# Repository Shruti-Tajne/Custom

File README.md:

# PCB
A simple LED ciruit with USB-C as power. Custom PCB for gifting

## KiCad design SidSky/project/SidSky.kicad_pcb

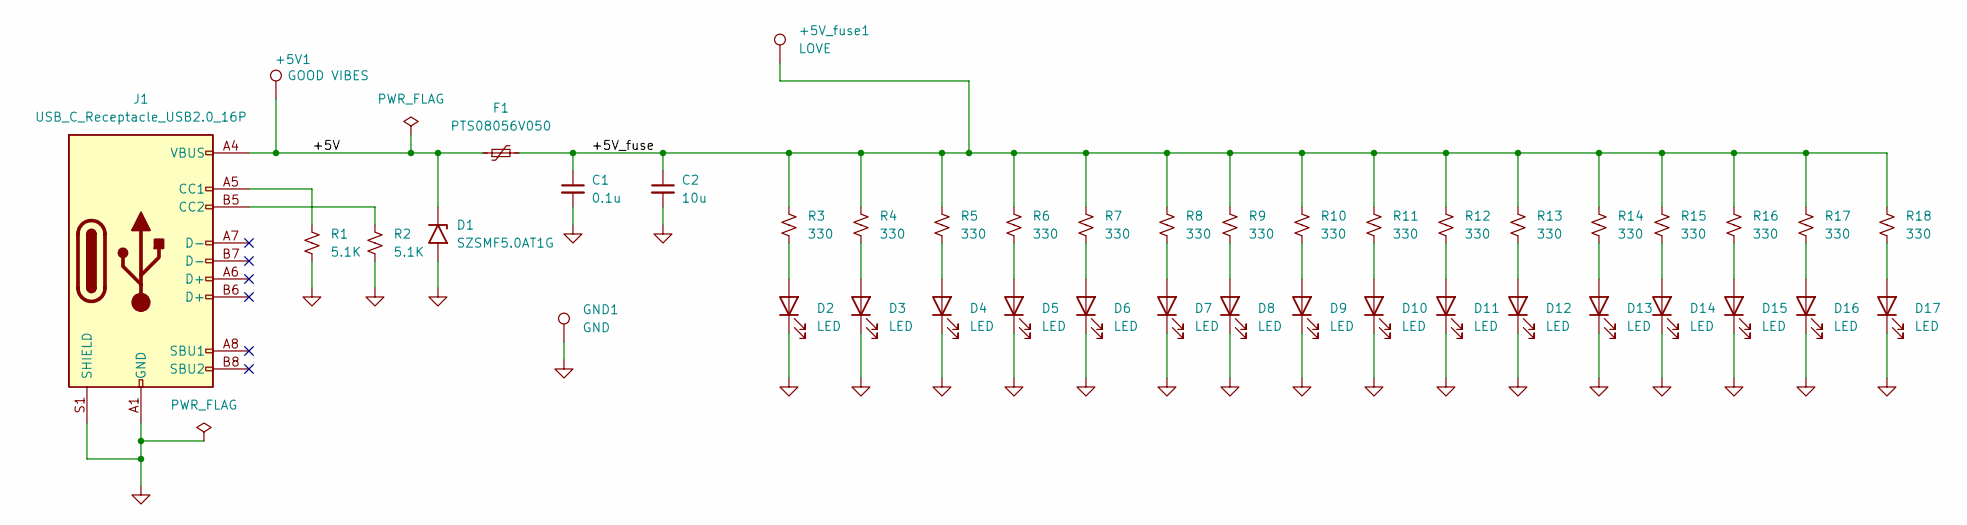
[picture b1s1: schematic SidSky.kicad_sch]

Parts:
+5V1: GOOD VIBES; TestPoint_Pad_D1.0mm; Manufacturer Part Number DNP
+5V_fuse1: LOVE; TestPoint_Pad_D1.0mm; Manufacturer Part Number DNP
C1: 0.1u; C_0805_2012Metric; Manufacturer Part Number CL21B104KBCNNNC
C2: 10u; C_0805_2012Metric; Manufacturer Part Number CL21A106KOQNNNE
D1: SZSMF5.0AT1G; D_SOD-123F; Manufacturer Part Number SZSMF5.0AT1G
D2, D3, D4, D5, D6, D7, D8, D9, D10, D11, D12, D13, D14, D15, D16, D17: LED; LED_0805_2012Metric_Pad1.15x1.40mm_HandSolder; Manufacturer Part Number LG R971-KN-1-0-20-R18
F1: PTS08056V050; Fuse_0805_2012Metric; Manufacturer Part Number PTS08056V050
GND1: GND; TestPoint_Pad_D1.0mm; Manufacturer Part Number DNP
J1: USB_C_Receptacle_USB2.0_16P; USB_C_Receptacle_GCT_USB4105-xx-A_16P_TopMnt_Horizontal; Manufacturer Part Number USB4105-GF-A
R1, R2: 5.1K; R_0805_2012Metric_Pad1.20x1.40mm_HandSolder; Manufacturer Part Number RMCF0805JT5K10
R3, R4, R5, R6, R7, R8, R9, R10, R11, R12, R13, R14, R15, R16, R17, R18: 330; R_0805_2012Metric_Pad1.20x1.40mm_HandSolder; Manufacturer Part Number RMCF0805JT330R

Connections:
/+5V: +5V1.1, D1.1 (A1), F1.1, J1.A4 (VBUS), J1.A9 (VBUS), J1.B4 (VBUS), J1.B9 (VBUS)
/+5V_fuse: +5V_fuse1.1, C1.1, C2.1, F1.2, R3.1, R4.1, R5.1, R6.1, R7.1, R8.1, R9.1, R10.1, R11.1, R12.1, R13.1, R14.1, R15.1, R16.1, R17.1, R18.1
GND: C1.2, C2.2, D1.2 (A2), D2.1 (K), D3.1 (K), D4.1 (K), D5.1 (K), D6.1 (K), D7.1 (K), D8.1 (K), D9.1 (K), D10.1 (K), D11.1 (K), D12.1 (K), D13.1 (K), D14.1 (K), D15.1 (K), D16.1 (K), D17.1 (K), GND1.1, J1.A1 (GND), J1.A12 (GND), J1.B1 (GND), J1.B12 (GND), J1.S1 (SHIELD), R1.2, R2.2
unnamed: D2.2 (A), R3.2
unnamed: D3.2 (A), R4.2
unnamed: D4.2 (A), R5.2
unnamed: D5.2 (A), R6.2
unnamed: D6.2 (A), R7.2
unnamed: D7.2 (A), R8.2
unnamed: D8.2 (A), R9.2
unnamed: D9.2 (A), R10.2
unnamed: D10.2 (A), R11.2
unnamed: D11.2 (A), R12.2
unnamed: D12.2 (A), R13.2
unnamed: D13.2 (A), R14.2
unnamed: D14.2 (A), R15.2
unnamed: D15.2 (A), R16.2
unnamed: D16.2 (A), R17.2
unnamed: D17.2 (A), R18.2
unnamed: J1.A5 (CC1), R1.1
unnamed: J1.B5 (CC2), R2.1

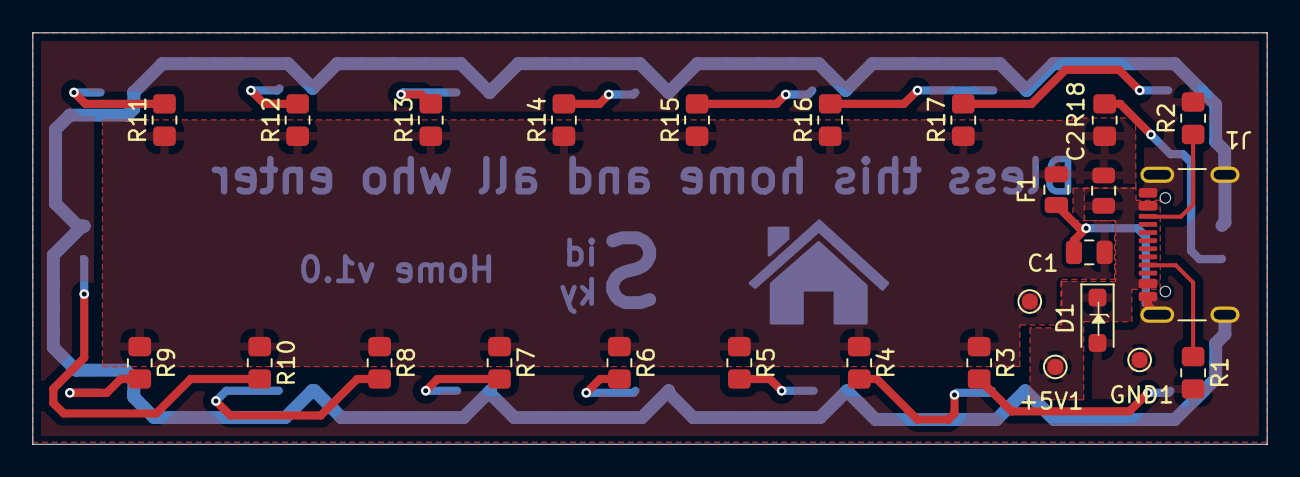
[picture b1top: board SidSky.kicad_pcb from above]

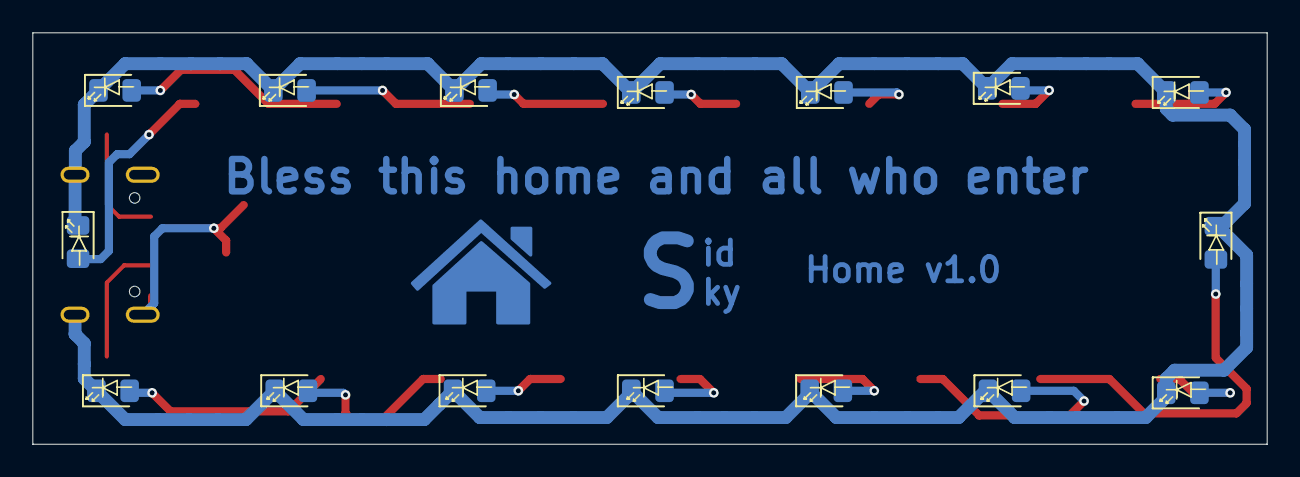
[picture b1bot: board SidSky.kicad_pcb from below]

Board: 2 copper layers, 76.2 x 25.4 mm, 42 parts (16 on the bottom side), 21 nets.

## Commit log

2026-03-13 intial commit
2026-03-13 make folders
2026-03-17 remove logo
2026-03-17 run drc
2026-03-17 update license to cern ohl
2026-03-17 add cern ohl
2026-03-17 SidSky pro start
2026-03-26 routing
